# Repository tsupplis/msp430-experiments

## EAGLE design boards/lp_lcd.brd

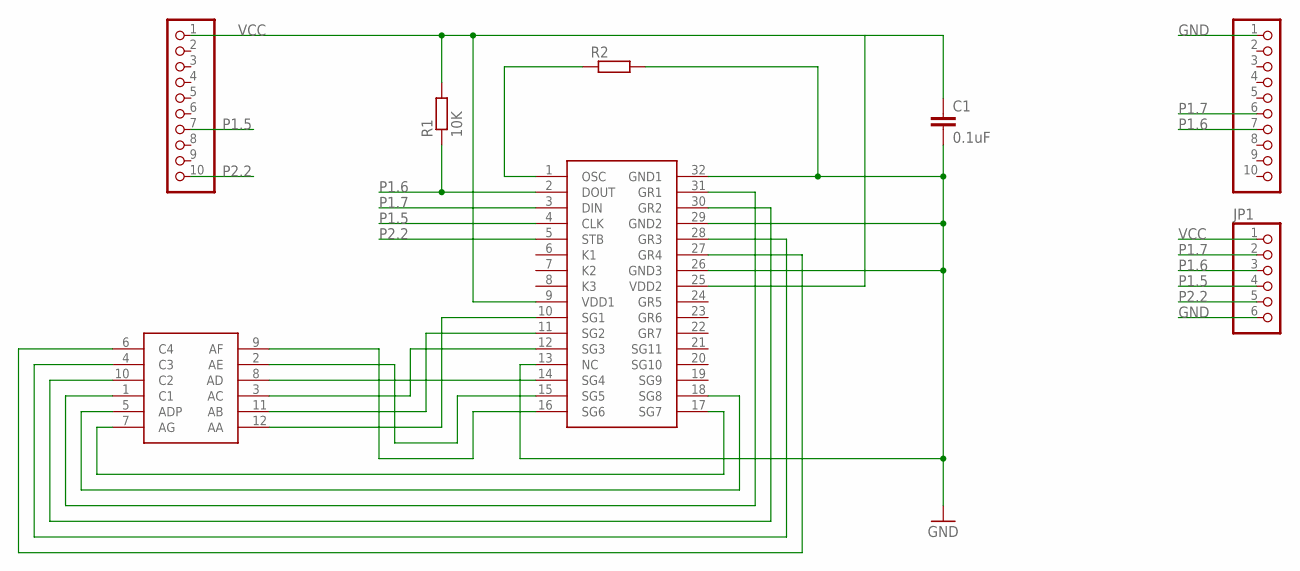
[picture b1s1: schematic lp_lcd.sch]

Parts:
C1: 0.1uF; C0805
J1: J1; 1X10
J2: J2; 1X10
JP1: PINHD-1X6; 1X06
R1: 10K; R0805
R2: R-EU_R0805; R0805
U$1: PT6961
U$2: HP5082-7414

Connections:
GND: C1.2, J2.1, JP1.6, R2.2, U$1.13 (NC), U$1.26 (GND3), U$1.29 (GND2), U$1.32 (GND1)
unnamed: U$1.10 (SG1), U$2.12 (AA)
unnamed: R2.1, U$1.1 (OSC)
unnamed: U$1.11 (SG2), U$2.11 (AB)
unnamed: U$1.12 (SG3), U$2.3 (AC)
unnamed: U$1.14 (SG4), U$2.8 (AD)
unnamed: U$1.15 (SG5), U$2.2 (AE)
unnamed: U$1.16 (SG6), U$2.9 (AF)
unnamed: U$1.17 (SG7), U$2.7 (AG)
unnamed: U$1.18 (SG8), U$2.5 (ADP)
unnamed: U$1.31 (GR1), U$2.1 (C1)
unnamed: U$1.30 (GR2), U$2.10 (C2)
unnamed: U$1.28 (GR3), U$2.4 (C3)
unnamed: U$1.27 (GR4), U$2.6 (C4)
P1.5: J1.7, JP1.4, U$1.4 (CLK)
P1.6: J2.7, JP1.3, R1.1, U$1.2 (DOUT)
P1.7: J2.6, JP1.2, U$1.3 (DIN)
P2.2: J1.10, JP1.5, U$1.5 (STB)
VCC: C1.1, J1.1, JP1.1, R1.2, U$1.9 (VDD1), U$1.25 (VDD2)

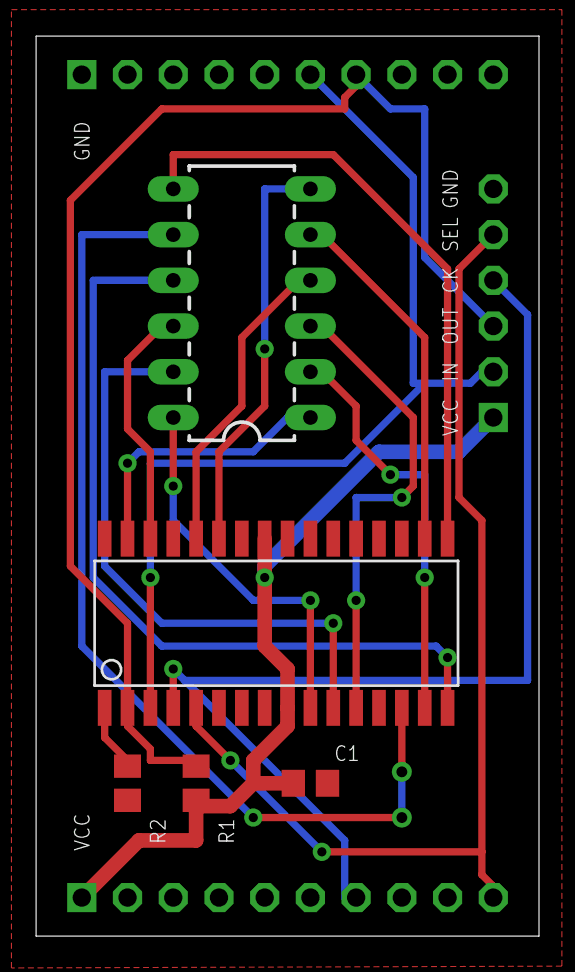
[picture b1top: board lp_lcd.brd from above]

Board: 2 copper layers, 27.9 x 50.0 mm, 8 parts (0 on the bottom side), 19 nets.

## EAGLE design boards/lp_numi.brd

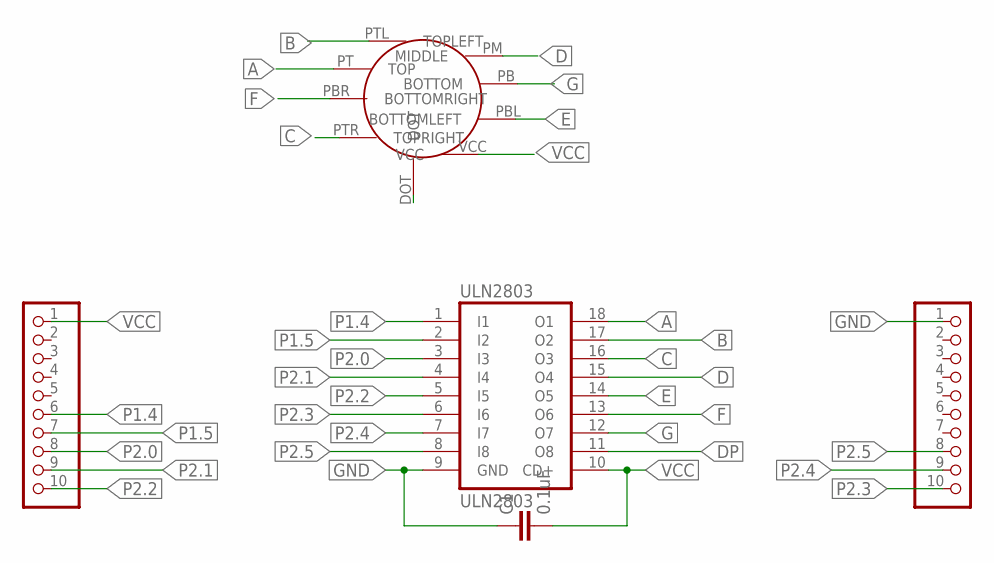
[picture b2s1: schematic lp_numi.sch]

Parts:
C1: 0.1uF; C025-025X050
J1: J1; 1X10
J2: J2; 1X10
U$2: IV16TINY_NUMITRON; IV16TINY_NUMITRON_PAC
ULN2803: ULN2803; DIL18

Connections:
A: U$2.PT (TOP), ULN2803.18 (O1)
B: U$2.PTL (TOPLEFT), ULN2803.17 (O2)
C: U$2.PTR (TOPRIGHT), ULN2803.16 (O3)
D: U$2.PM (MIDDLE), ULN2803.15 (O4)
DP: U$2.DOT, ULN2803.11 (O8)
E: U$2.PBL (BOTTOMLEFT), ULN2803.14 (O5)
F: U$2.PBR (BOTTOMRIGHT), ULN2803.13 (O6)
G: U$2.PB (BOTTOM), ULN2803.12 (O7)
GND: C1.1, J2.1, ULN2803.9 (GND)
P1.4: J1.6, ULN2803.1 (I1)
P1.5: J1.7, ULN2803.2 (I2)
P2.0: J1.8, ULN2803.3 (I3)
P2.1: J1.9, ULN2803.4 (I4)
P2.2: J1.10, ULN2803.5 (I5)
P2.3: J2.10, ULN2803.6 (I6)
P2.4: J2.9, ULN2803.7 (I7)
P2.5: J2.8, ULN2803.8 (I8)
VCC: C1.2, J1.1, U$2.VCC, ULN2803.10 (CD+)

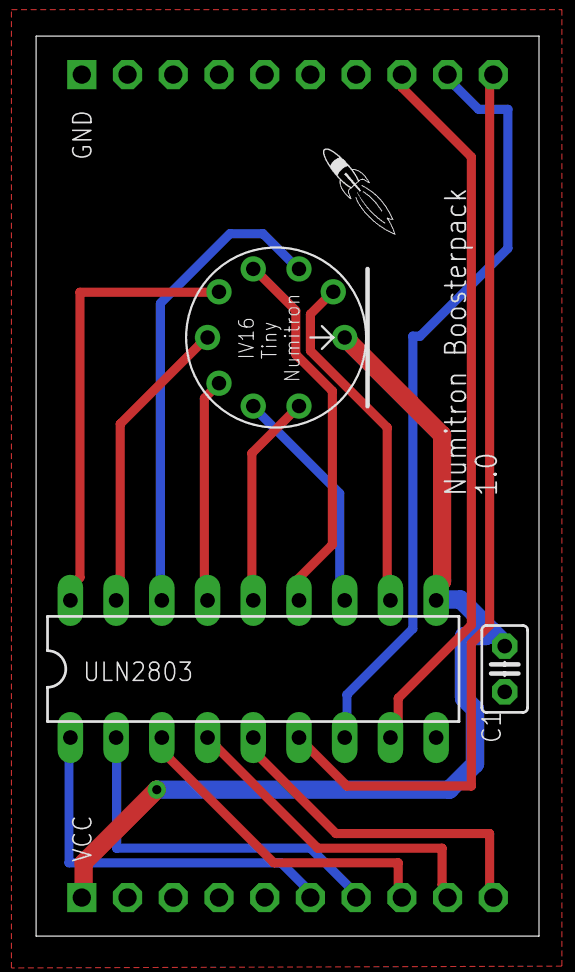
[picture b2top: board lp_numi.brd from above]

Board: 2 copper layers, 27.9 x 50.0 mm, 6 parts (0 on the bottom side), 18 nets.

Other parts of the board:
U$1: LOGO-ROCKET

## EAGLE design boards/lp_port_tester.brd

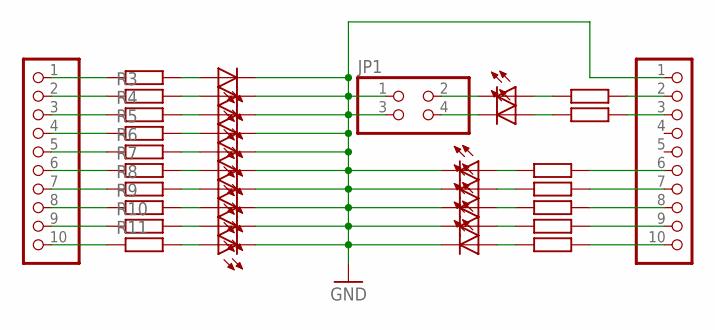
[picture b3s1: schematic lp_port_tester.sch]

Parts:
J1: J1; 1X10
J2: J2; 1X10
JP1: PINHD-2X2; 2X02
PWR, PWR1, PWR2, PWR3, PWR4, PWR5, PWR6, PWR7, PWR8, PWR9, PWR10, PWR11, PWR14, PWR15, PWR16, PWR17, PWR18: PWR; CHIPLED_1206
R1, R2, R3, R4, R5, R6, R7, R8, R9, R10, R11, R12, R15, R16, R17, R18, R19: 470; R0805

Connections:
GND: J2.1, JP1.1, JP1.3, PWR1.C, PWR2.C, PWR3.C, PWR4.C, PWR5.C, PWR6.C, PWR7.C, PWR8.C, PWR9.C, PWR10.C, PWR14.C, PWR15.C, PWR16.C, PWR17.C, PWR18.C
unnamed: PWR1.A, R1.2
unnamed: PWR.A, R2.2
unnamed: PWR2.A, R3.2
unnamed: PWR3.A, R4.2
unnamed: PWR4.A, R5.2
unnamed: PWR5.A, R6.2
unnamed: PWR6.A, R7.2
unnamed: PWR7.A, R8.2
unnamed: PWR8.A, R9.2
unnamed: PWR9.A, R10.2
unnamed: PWR10.A, R11.2
unnamed: PWR11.A, R12.2
unnamed: J1.4, R5.1
unnamed: J1.5, R6.1
unnamed: PWR14.A, R15.2
unnamed: PWR15.A, R16.2
unnamed: PWR16.A, R17.2
unnamed: PWR17.A, R18.2
unnamed: PWR18.A, R19.2
unnamed: J1.1, R1.1
unnamed: J1.2, R3.1
unnamed: J2.2, R2.1
unnamed: J2.3, R12.1
unnamed: J1.9, R10.1
unnamed: J1.10, R11.1
unnamed: J1.3, R4.1
unnamed: J1.8, R9.1
unnamed: J2.6, R15.1
unnamed: J2.7, R16.1
unnamed: J2.8, R17.1
unnamed: J2.9, R18.1
unnamed: J2.10, R19.1
unnamed: J1.7, R8.1
unnamed: J1.6, R7.1
unnamed: JP1.2, PWR.C
unnamed: JP1.4, PWR11.C

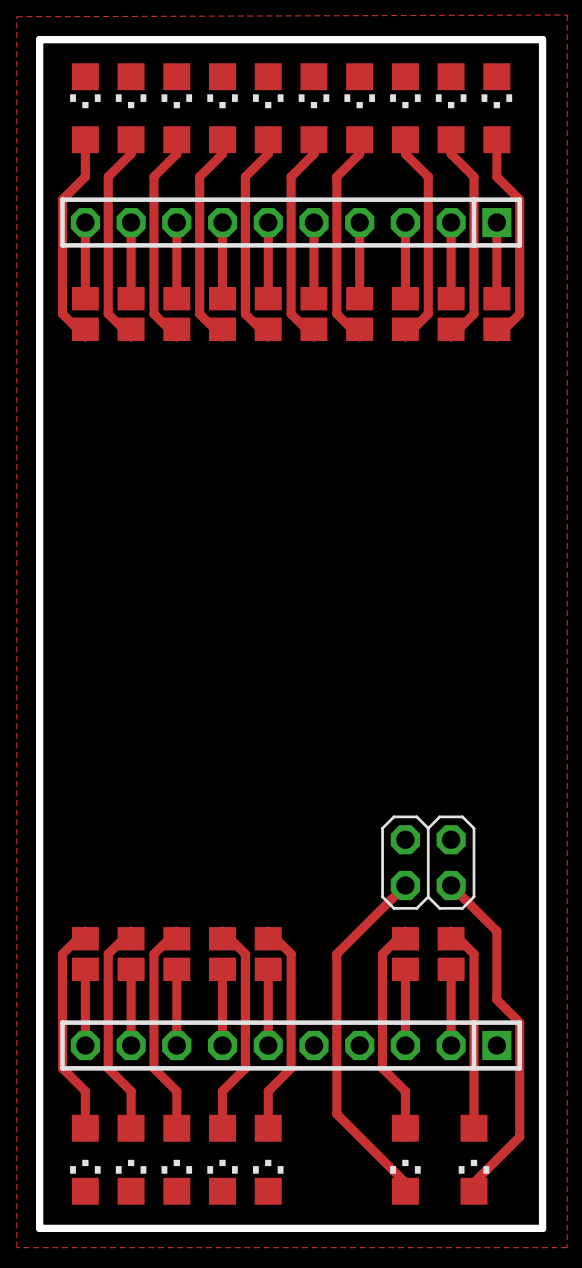
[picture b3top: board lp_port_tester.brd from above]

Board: 2 copper layers, 27.9 x 66.0 mm, 37 parts (0 on the bottom side), 37 nets.

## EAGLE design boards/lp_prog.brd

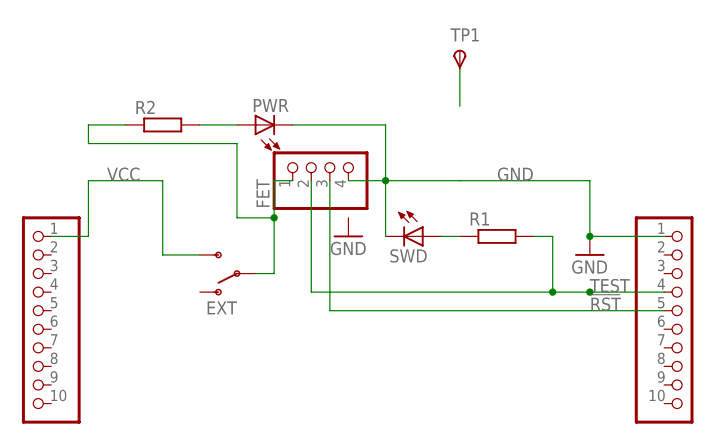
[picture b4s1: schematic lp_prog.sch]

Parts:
FET: FET; 1X04
J1: J1; 1X10
J2: J2; 1X10
ON: EXT; SWITCH-SPDT
PWR: PWR; CHIPLED_1206
R1, R2: 470; R0805
SWD: SWD; CHIPLED_1206
TP1: TPSTP20R; TP20R

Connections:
!RST: FET.3, J2.5
GND: FET.4, J2.1, PWR.C, SWD.C
unnamed: R1.1, SWD.A
unnamed: PWR.A, R2.2
unnamed: FET.1, ON.2, R2.1
TEST: FET.2, J2.4, R1.2
VCC: J1.1, ON.3 (S)

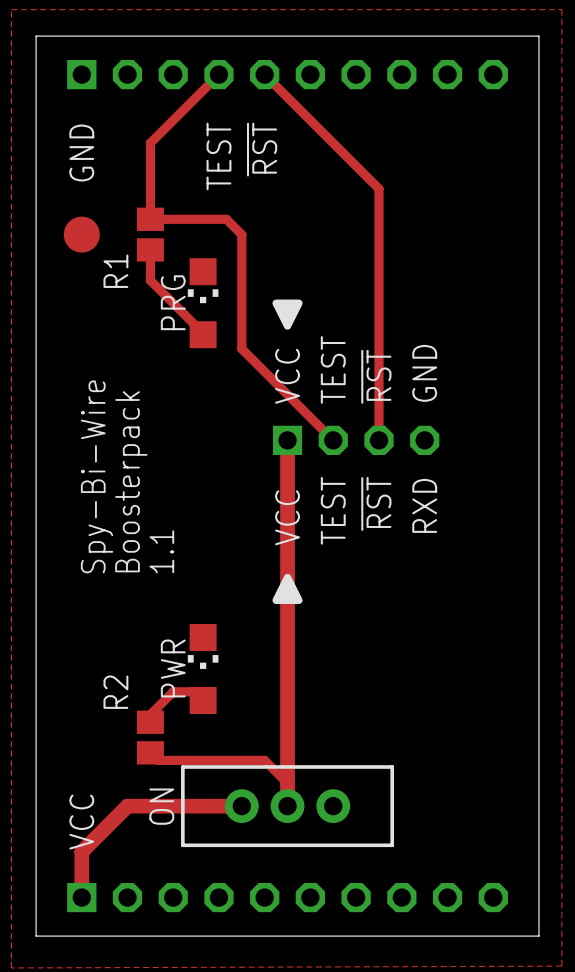
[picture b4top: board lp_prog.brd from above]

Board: 2 copper layers, 27.9 x 50.0 mm, 9 parts (0 on the bottom side), 7 nets.

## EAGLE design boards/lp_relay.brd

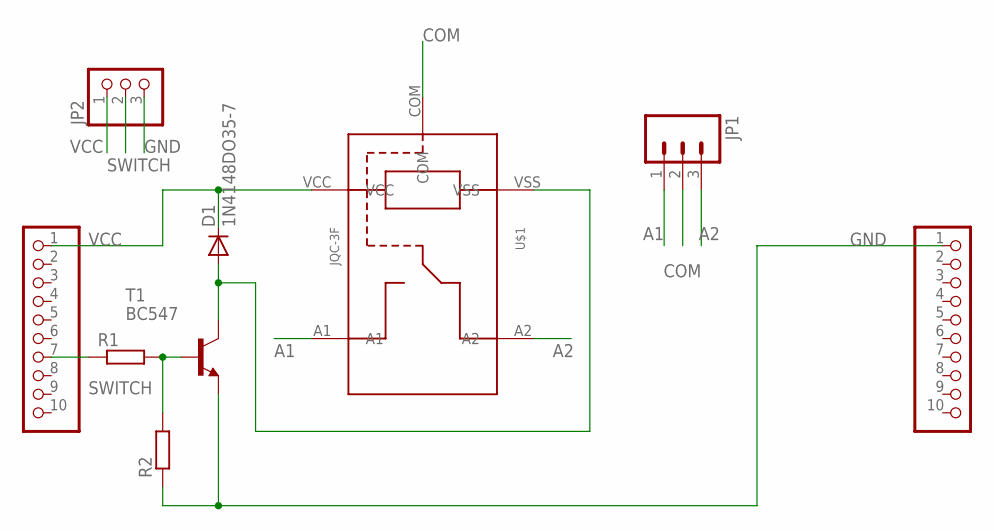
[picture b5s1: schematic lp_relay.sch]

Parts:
D1: 1N4148DO35-7; DO35-7
J1: J1; 1X10
J2: J2; 1X10
JP1: M03-SCREW-5MM; SCREWTERMINAL-5MM-3
JP2: PINHD-1X3; 1X03
R1, R2: R-EU_0207/10; 0207/10
T1: BC547; TO92
U$1: JQC-3F

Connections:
A1: JP1.1, U$1.A1
A2: JP1.3, U$1.A2
COM: JP1.2, U$1.COM
GND: J2.1, JP2.3, R2.1, T1.1 (E)
unnamed: R1.2, R2.2, T1.2 (B)
unnamed: D1.A, T1.3 (C), U$1.VSS
SWITCH: J1.7, JP2.2, R1.1
VCC: D1.C, J1.1, JP2.1, U$1.VCC

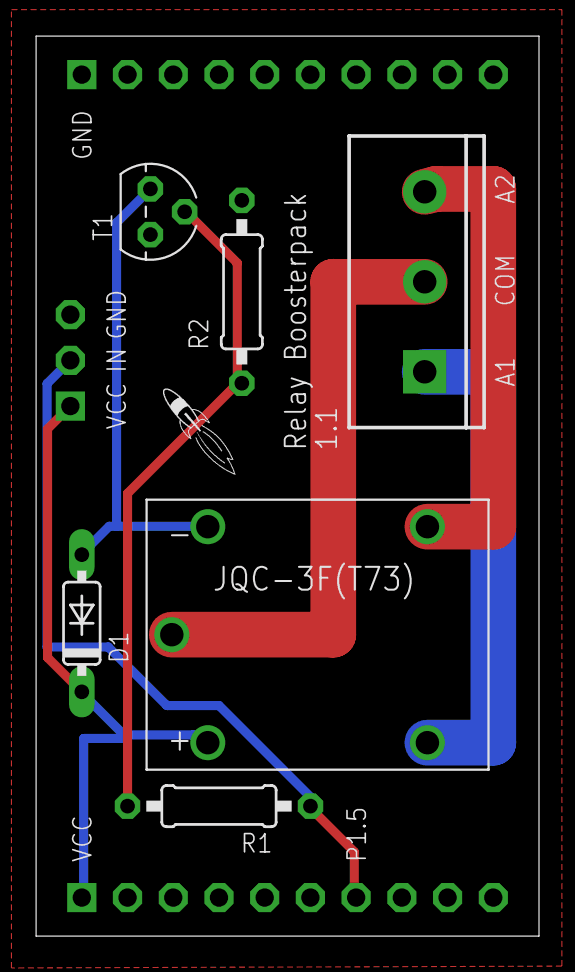
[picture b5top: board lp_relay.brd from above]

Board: 2 copper layers, 27.9 x 50.0 mm, 10 parts (0 on the bottom side), 8 nets.

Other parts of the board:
U$2: LOGO-ROCKET

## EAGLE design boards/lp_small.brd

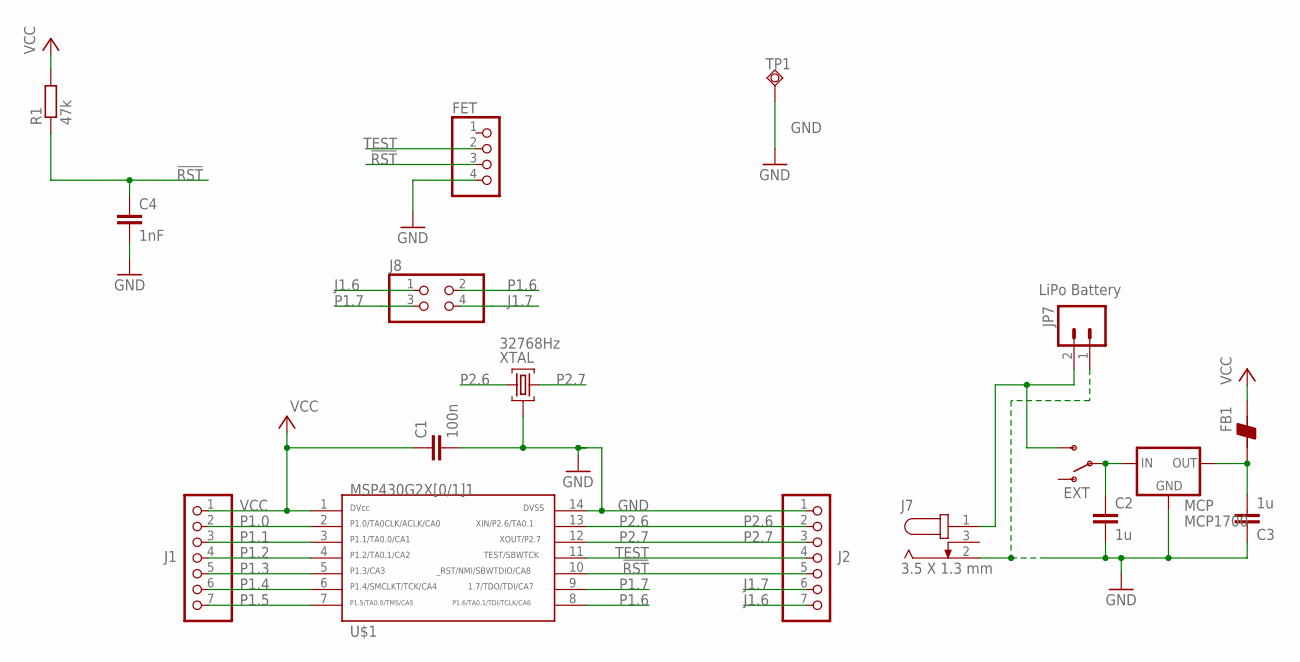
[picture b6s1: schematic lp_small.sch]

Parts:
C1: 100n; C0805
C2, C3: 1u; C0805
C4: 1nF; C0805
FB1: BEAD-0805; 0805
FET: PINHD-1X4; 1X04
J1, J2: PINHD-1X7; 1X07
J7: 3.5 X 1.3 mm; 3.5X1.3MM_DC_JACK
J8: PINHD-2X2; 2X02
JP7: LiPo Battery; JST-2-PTH
MCP: MCP1700; SOT-23
ON: EXT; SWITCH-SPDT
R1: 47k; R0805
TP1: TPSQTP20R; TP20R
U$1: G2X[0/1]1---N14; N14
XTAL: 32768Hz; QUARZ5

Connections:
!RST: C4.1, FET.3, J2.5, R1.1, U$1.10
GND: C1.2, C2.2, C3.1, C4.2, FET.4, J2.1, J7.2, JP7.1, MCP.1 (GND), TP1.TP, U$1.14, XTAL.GND@0 (0)
J1.6: J2.7, J8.1
J1.7: J2.6, J8.4
unnamed: C2.1, MCP.3 (IN), ON.2
unnamed: C3.2, FB1.1, MCP.2 (OUT)
P1.0: J1.2, U$1.2
P1.1: J1.3, U$1.3
P1.2: J1.4, U$1.4
P1.3: J1.5, U$1.5
P1.4: J1.6, U$1.6
P1.5: J1.7, U$1.7
P1.6: J8.2, U$1.8
P1.7: J8.3, U$1.9
P2.6: J2.2, U$1.13, XTAL.2
P2.7: J2.3, U$1.12, XTAL.1
TEST: FET.2, J2.4, U$1.11
VCC: C1.1, FB1.2, J1.1, R1.2, U$1.1
VCCEXT: J7.1, JP7.2, ON.3 (S)

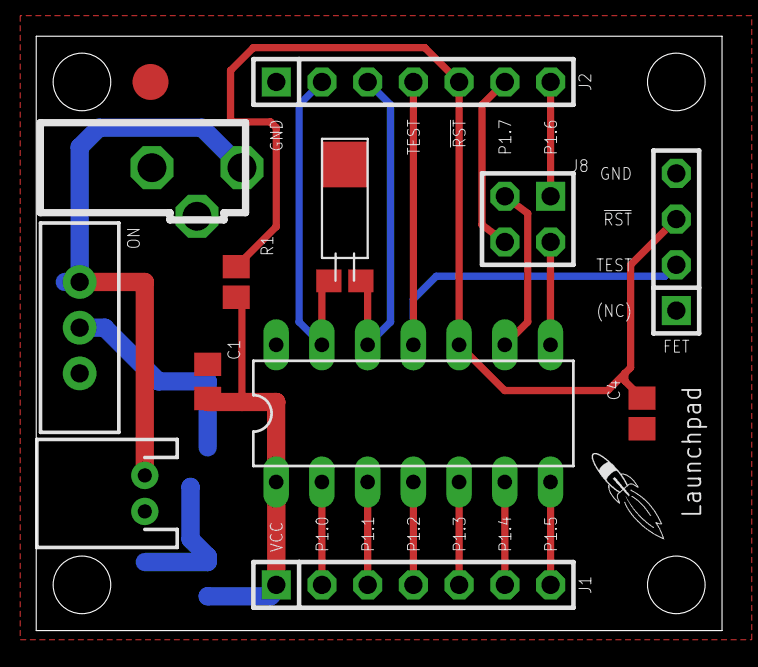
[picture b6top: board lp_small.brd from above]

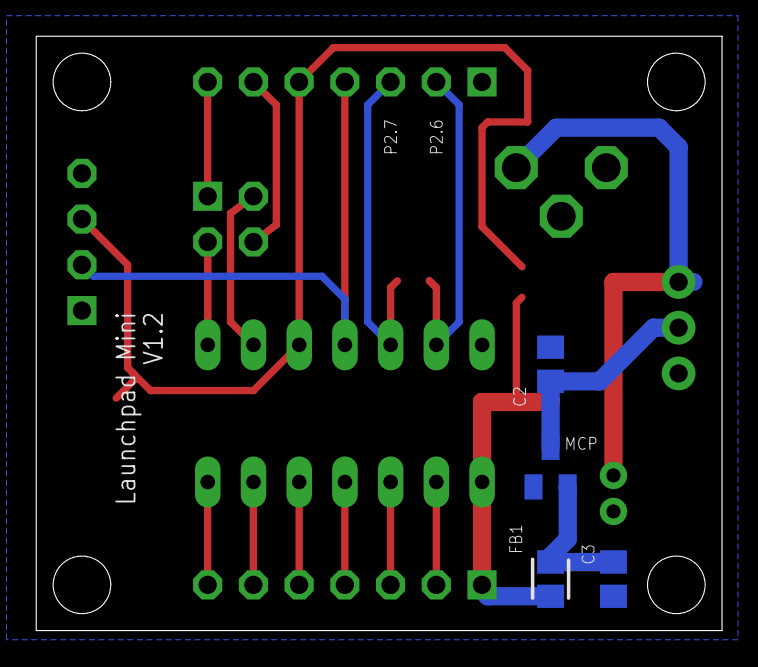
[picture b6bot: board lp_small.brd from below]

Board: 2 copper layers, 38.1 x 33.0 mm, 18 parts (4 on the bottom side), 19 nets.

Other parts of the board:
U$2: LOGO-ROCKET

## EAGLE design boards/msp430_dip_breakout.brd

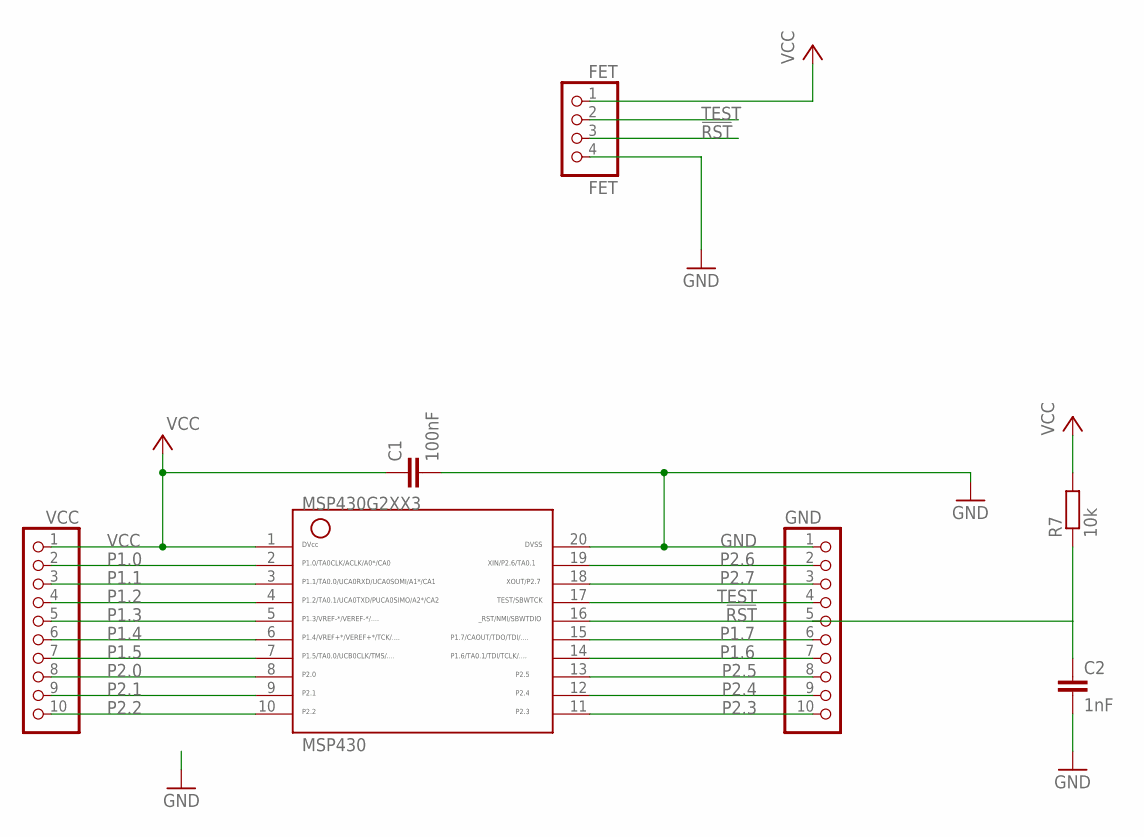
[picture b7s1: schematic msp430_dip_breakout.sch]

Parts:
C1: 100nF; C0805
C2: 1nF; C0805
FET: FET; 1X04
GND: PH1X10OCT076; PH1X10OCT76
MSP430: MSP430N; DIP20_HEX
R7: 10k; R0805
VCC: PH1X10OCT076; PH1X10OCT76

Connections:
!RST: C2.1, FET.3, GND.5, MSP430.16, R7.1
GND: C1.2, C2.2, FET.4, GND.1, MSP430.20
P1.0: MSP430.2, VCC.2
P1.1: MSP430.3, VCC.3
P1.2: MSP430.4, VCC.4
P1.3: MSP430.5, VCC.5
P1.4: MSP430.6, VCC.6
P1.5: MSP430.7, VCC.7
P1.6: GND.7, MSP430.14
P1.7: GND.6, MSP430.15
P2.0: MSP430.8, VCC.8
P2.1: MSP430.9, VCC.9
P2.2: MSP430.10, VCC.10
P2.3: GND.10, MSP430.11
P2.4: GND.9, MSP430.12
P2.5: GND.8, MSP430.13
P2.6: GND.2, MSP430.19
P2.7: GND.3, MSP430.18
TEST: FET.2, GND.4, MSP430.17
VCC: C1.1, FET.1, MSP430.1, R7.2, VCC.1

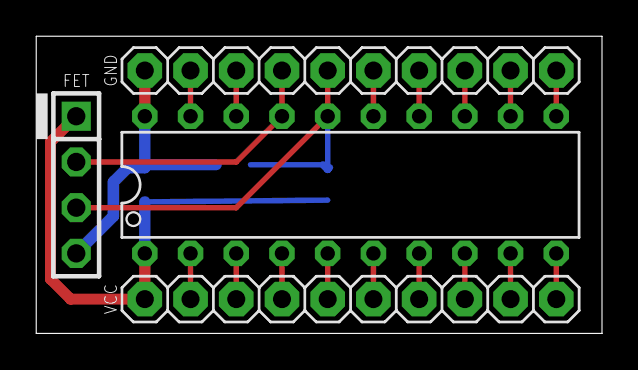
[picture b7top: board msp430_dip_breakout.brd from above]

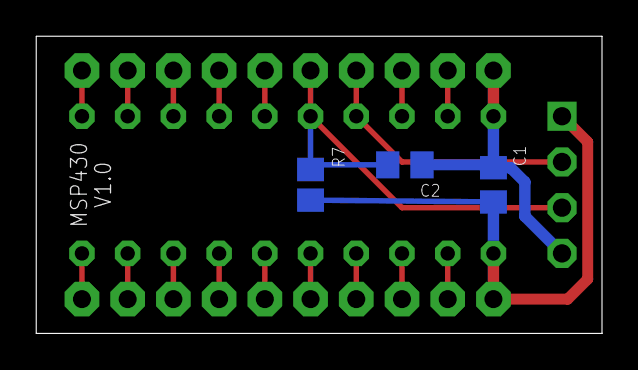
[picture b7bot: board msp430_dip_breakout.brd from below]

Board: 2 copper layers, 31.4 x 16.5 mm, 7 parts (3 on the bottom side), 20 nets.

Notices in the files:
parts and their libraries:
SparkFun: Licensing: CC v3.0 Share-Alike You are welcome to use this library for commercial purposes.
